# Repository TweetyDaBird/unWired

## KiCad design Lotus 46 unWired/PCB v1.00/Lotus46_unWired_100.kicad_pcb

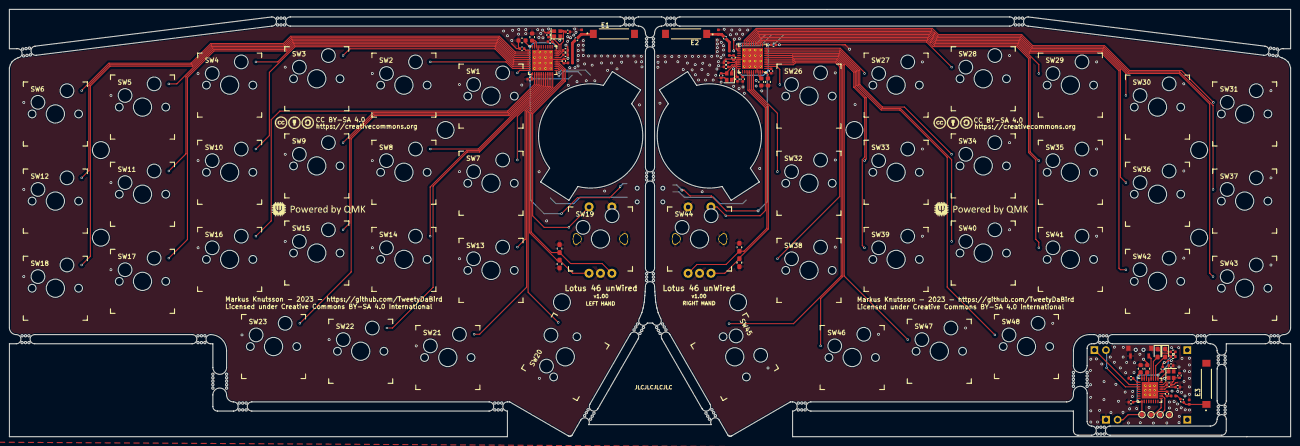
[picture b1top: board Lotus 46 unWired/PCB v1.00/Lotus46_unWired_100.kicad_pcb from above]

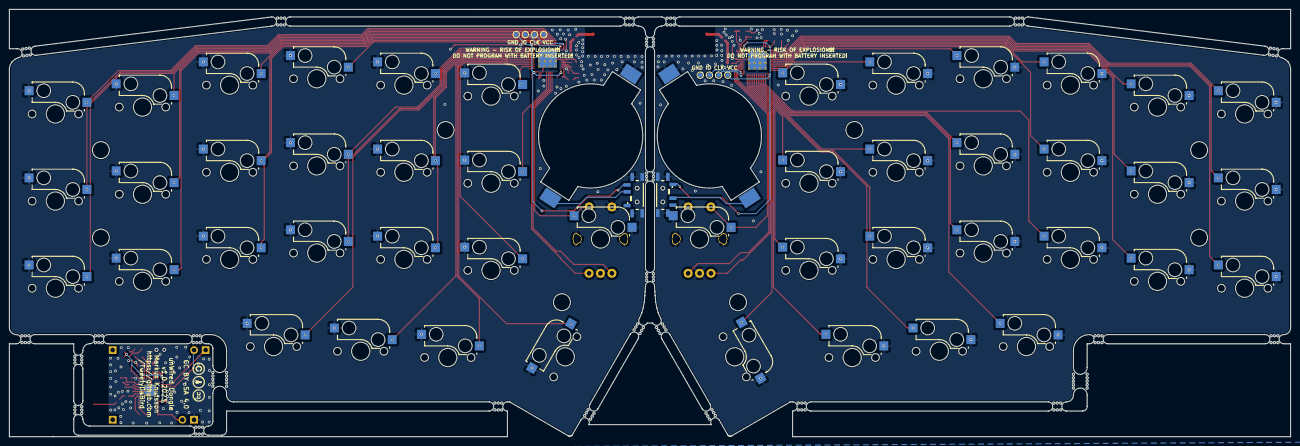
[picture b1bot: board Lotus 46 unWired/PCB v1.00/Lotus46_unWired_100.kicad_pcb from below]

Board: 2 copper layers, 280.1 x 93.4 mm, 164 parts (17 on the bottom side), 96 nets.

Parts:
BT1, BT2: Battery_Cell; BS-12
C1, C2, C7, C14, C15, C20, C30, C31, C32: 100nF; C_0402_1005Metric
C3, C16, C33: 4.7uF; C_0603_1608Metric
C4, C17, C27: 1uF; C_0603_1608Metric
C5, C18, C28: 100pF; C_0402_1005Metric
C6, C19, C29: DNP; C_0402_1005Metric
C8, C21, C34: 1.5pF; C_0402_1005Metric
C9, C22, C35: 0.8pF; C_0402_1005Metric
C10, C11, C23, C24: 100nF; C_0603_1608Metric_Pad1.08x0.95mm_HandSolder
C12, C13, C25, C26, C36, C37: 12pF; C_0402_1005Metric
E1, E2, E3: 2450AT45A100E; ANT_2450AT45A100E
J1, J2: Conn_01x02; Pinheader_2
J3, J4: Conn_01x01; PinHeader_1
L1, L2, L3, L4, L5, L6: 3.9nH; L_0402_1005Metric
LED1: RED; LED_0603_1608Metric_Pad1.05x0.95mm_HandSolder
LED2: GREEN; LED_0603_1608Metric_Pad1.05x0.95mm_HandSolder
Logo1, Logo3: QMK_Logo; qmk logo
Logo2, Logo4, Logo5: License; CC_BY_SA_40_line
PAIR1: TS-A002; YTS-A002
R1, R2: 220; R_0402_1005Metric
SW1, SW2, SW3, SW4, SW5, SW6, SW7, SW8, SW9, SW10, SW11, SW12, SW13, SW14, SW15, SW16, SW17, SW18, SW20, SW21, SW22, SW23, SW26, SW27, SW28, SW29, SW30, SW31, SW32, SW33, SW34, SW35, SW36, SW37, SW38, SW39, SW40, SW41, SW42, SW43, SW45, SW46, SW47, SW48: Switch; SW_MX_HotSwap
SW19, SW44: Switch; SW_MX_HotSwap_FOR ENCODER
SW24, SW49: Rotary_Encoder_Switch; Encoder_Alps_EC11E_Small
SW25, SW50: MSK12C02
TH1, TH2, TH3, TH4, TH5, TH6, TH7, TH8: HOLE; Spacer PCB hole
TP1, TP2, TP3, TP4, TP5, TP6, TP7, TP8, TP9, TP10, TP11, TP12: TestPoint; TestPoint_Pad_D1.0mm
U1, U2: nRF52810-QFxx; QFN-48-1EP_6x6mm_P0.4mm_EP4.6x4.6mm_ThermalVias
U3: nRF52810-QCxx; QFN-32-1EP_5x5mm_P0.5mm_EP3.6x3.6mm_ThermalVias
Y1, Y2, Y3: 7F32000E08UCG; Crystal_SMD_2016-4Pin_2.0x1.6mm
mouse-bite-2mm-slot, mouse-bite-2mm-slot#2, mouse-bite-2mm-slot#3, mouse-bite-2mm-slot#4, mouse-bite-2mm-slot#5, mouse-bite-2mm-slot#6, mouse-bite-2mm-slot#7, mouse-bite-2mm-slot#8, mouse-bite-2mm-slot#9, mouse-bite-2mm-slot#10, mouse-bite-2mm-slot#11, mouse-bite-2mm-slot#12, mouse-bite-2mm-slot#13, mouse-bite-2mm-slot#14, mouse-bite-2mm-slot#15, mouse-bite-2mm-slot#16, mouse-bite-2mm-slot#17, mouse-bite-2mm-slot#18, mouse-bite-2mm-slot#19, mouse-bite-2mm-slot#20, mouse-bite-2mm-slot#21, mouse-bite-2mm-slot#22, mouse-bite-2mm-slot#23, mouse-bite-2mm-slot#24: VAL**; mouse-bite-2mm-slot
mouse-bite-3mm-slot, mouse-bite-3mm-slot#2: VAL**; mouse-bite-3mm-slot

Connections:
+3V3: C31.2, C32.2, C33.2, J2.2, R1.2, R2.2, TP9.1, U3.9 (VDD), U3.25 (VDD), U3.32 (VDD)
/Dongle/SCL: J1.2, U3.3 (P0.01/XL2)
/Dongle/SDA: J1.1, U3.2 (P0.00/XL1)
/Dongle/SWDCLK: TP10.1, U3.17 (SWDCLK)
/Dongle/SWDIO: TP11.1, U3.18 (SWDIO)
/Left Matrix/3V3: C1.2, C2.2, C3.2, SW25.NC, TP1.1, U1.13 (VDD), U1.36 (VDD), U1.48 (VDD)
/Left Matrix/EncA: C10.1, SW24.A, U1.27 (P0.22)
/Left Matrix/EncB: C11.2, SW24.B, U1.28 (P0.23)
/Left Matrix/SW1: SW1.2, U1.12 (P0.10)
/Left Matrix/SW2: SW2.2, U1.11 (P0.09)
/Left Matrix/SW3: SW3.2, U1.10 (P0.08)
/Left Matrix/SW4: SW4.2, U1.8 (P0.06)
/Left Matrix/SW5: SW5.2, U1.5 (P0.03/AIN1)
/Left Matrix/SW6: SW6.2, U1.2 (P0.00/XL1)
/Left Matrix/SW7: SW7.2, U1.21 (P0.18)
/Left Matrix/SW8: SW8.2, U1.18 (P0.15)
/Left Matrix/SW9: SW9.2, U1.15 (P0.12)
/Left Matrix/SW10: SW10.2, U1.9 (P0.07)
/Left Matrix/SW11: SW11.2, U1.6 (P0.04/AIN2)
/Left Matrix/SW12: SW12.2, U1.3 (P0.01/XL2)
/Left Matrix/SW13: SW13.2, U1.22 (P0.19)
/Left Matrix/SW14: SW14.2, U1.19 (P0.16)
/Left Matrix/SW15: SW15.2, U1.16 (P0.13)
/Left Matrix/SW16: SW16.2, U1.14 (P0.11)
/Left Matrix/SW17: SW17.2, U1.7 (P0.05/AIN3)
/Left Matrix/SW18: SW18.2, U1.4 (P0.02/AIN0)
/Left Matrix/SW19: SW19.1, SW24.S2, U1.29 (P0.24)
/Left Matrix/SW20: SW20.2, U1.24 (P0.21/~RESET)
/Left Matrix/SW21: SW21.2, U1.23 (P0.20)
/Left Matrix/SW22: SW22.2, U1.20 (P0.17)
/Left Matrix/SW23: SW23.2, U1.17 (P0.14)
/Left Matrix/SWCLK: TP2.1, U1.25 (SWDCLK)
/Left Matrix/SWDIO: TP3.1, U1.26 (SWDIO)
/Right Matrix/3V3: C14.2, C15.2, C16.2, SW50.NO, TP5.1, U2.13 (VDD), U2.36 (VDD), U2.48 (VDD)
/Right Matrix/EncA: C23.1, SW49.A, U2.41 (P0.29/AIN5)
/Right Matrix/EncB: C24.2, SW49.B, U2.42 (P0.30/AIN6)
/Right Matrix/SW1: SW26.1, U2.2 (P0.00/XL1)
/Right Matrix/SW2: SW27.1, U2.12 (P0.10)
/Right Matrix/SW3: SW28.1, U2.14 (P0.11)
/Right Matrix/SW4: SW29.1, U2.17 (P0.14)
/Right Matrix/SW5: SW30.1, U2.20 (P0.17)
/Right Matrix/SW6: SW31.1, U2.23 (P0.20)
/Right Matrix/SW7: SW32.1, U2.43 (P0.31/AIN7)
/Right Matrix/SW8: SW33.1, U2.8 (P0.06)
/Right Matrix/SW9: SW34.1, U2.11 (P0.09)
/Right Matrix/SW10: SW35.1, U2.16 (P0.13)
/Right Matrix/SW11: SW36.1, U2.19 (P0.16)
/Right Matrix/SW12: SW37.1, U2.22 (P0.19)
/Right Matrix/SW13: SW38.1, U2.3 (P0.01/XL2)
/Right Matrix/SW14: SW39.1, U2.7 (P0.05/AIN3)
/Right Matrix/SW15: SW40.1, U2.10 (P0.08)
/Right Matrix/SW16: SW41.1, U2.15 (P0.12)
/Right Matrix/SW17: SW42.1, U2.18 (P0.15)
/Right Matrix/SW18: SW43.1, U2.21 (P0.18)
/Right Matrix/SW19: SW44.2, SW49.S1, U2.40 (P0.28/AIN4)
/Right Matrix/SW20: SW45.1, U2.4 (P0.02/AIN0)
/Right Matrix/SW21: SW46.1, U2.5 (P0.03/AIN1)
/Right Matrix/SW22: SW47.1, U2.6 (P0.04/AIN2)
/Right Matrix/SW23: SW48.1, U2.9 (P0.07)
/Right Matrix/SWCLK: TP6.1, U2.25 (SWDCLK)
/Right Matrix/SWDIO: TP7.1, U2.26 (SWDIO)
GND: BT1.2 (-), BT2.2 (-), C1.1, C2.1, C3.1, C4.1, C5.1, C6.1, C7.1, C9.1, C10.2, C11.1, C12.1, C13.2, C14.1, C15.1, C16.1, C17.1, C18.1, C19.1, C20.1, C22.1, C23.2, C24.1, C25.1, C26.2, C27.1, C28.1, C29.1, C30.1, C31.1, C32.1, C33.1, C35.1, C36.1, C37.2, J2.1, L2.1, L4.1, L6.1, PAIR1.1, PAIR1.3, SW1.1, SW2.1, SW3.1, SW4.1, SW5.1, SW6.1, SW7.1, SW8.1, SW9.1, SW10.1, SW11.1, SW12.1, SW13.1, SW14.1, SW15.1, SW16.1, SW17.1, SW18.1, SW19.2, SW19.3, SW20.1, SW21.1, SW22.1, SW23.1, SW24.C, SW24.MP1 (GND), SW24.MP2 (GND), SW24.S1, SW25.MP (GND), SW26.2, SW27.2, SW28.2, SW29.2, SW30.2, SW31.2, SW32.2, SW33.2, SW34.2, SW35.2, SW36.2, SW37.2, SW38.2, SW39.2, SW40.2, SW41.2, SW42.2, SW43.2, SW44.1, SW44.3, SW45.2, SW46.2, SW47.2, SW48.2, SW49.C, SW49.MP1 (GND), SW49.MP2 (GND), SW49.S2, SW50.MP (GND), TP4.1, TP8.1, TP12.1, U1.31 (VSS), U1.45 (VSS), U1.49 (VSS), U2.31 (VSS), U2.45 (VSS), U2.49 (VSS), U3.20 (VSS), U3.29 (VSS), U3.33 (VSS), Y1.2, Y1.4, Y2.2, Y2.4, Y3.2, Y3.4
unnamed: BT1.1 (+), SW25.COM
unnamed: BT2.1 (+), SW50.COM
unnamed: C8.1, L1.1
unnamed: C8.2, E1.1, L2.2
unnamed: C21.1, L3.1
unnamed: C21.2, E2.1, L4.2
unnamed: C34.1, L5.1
unnamed: C34.2, E3.1, L6.2
unnamed: LED1.2 (A), U3.26 (P0.25)
unnamed: LED1.1 (K), R1.1
unnamed: LED2.2 (A), U3.27 (P0.28/AIN4)
unnamed: LED2.1 (K), R2.1
unnamed: C9.2, L1.2, U1.30 (ANT)
unnamed: C4.2, U1.46 (DEC4), U1.47 (DCC)
unnamed: C7.2, U1.1 (DEC1)
unnamed: C6.2, U1.32 (DEC2)
unnamed: C5.2, U1.33 (DEC3)
unnamed: C12.2, U1.34 (XC1), Y1.3
unnamed: C13.1, U1.35 (XC2), Y1.1
unnamed: C22.2, L3.2, U2.30 (ANT)
unnamed: C17.2, U2.46 (DEC4), U2.47 (DCC)
unnamed: C20.2, U2.1 (DEC1)
unnamed: C19.2, U2.32 (DEC2)
unnamed: C18.2, U2.33 (DEC3)
unnamed: C25.2, U2.34 (XC1), Y2.3
unnamed: C26.1, U2.35 (XC2), Y2.1
unnamed: C35.2, L5.2, U3.19 (ANT)
unnamed: C27.2, U3.30 (DEC4), U3.31 (DCC)
unnamed: C30.2, U3.1 (DEC1)
unnamed: C29.2, U3.21 (DEC2)
unnamed: C28.2, U3.22 (DEC3)
unnamed: PAIR1.2, U3.28 (P0.30/AIN6)
unnamed: C36.2, U3.23 (XC1), Y3.3
unnamed: C37.1, U3.24 (XC2), Y3.1

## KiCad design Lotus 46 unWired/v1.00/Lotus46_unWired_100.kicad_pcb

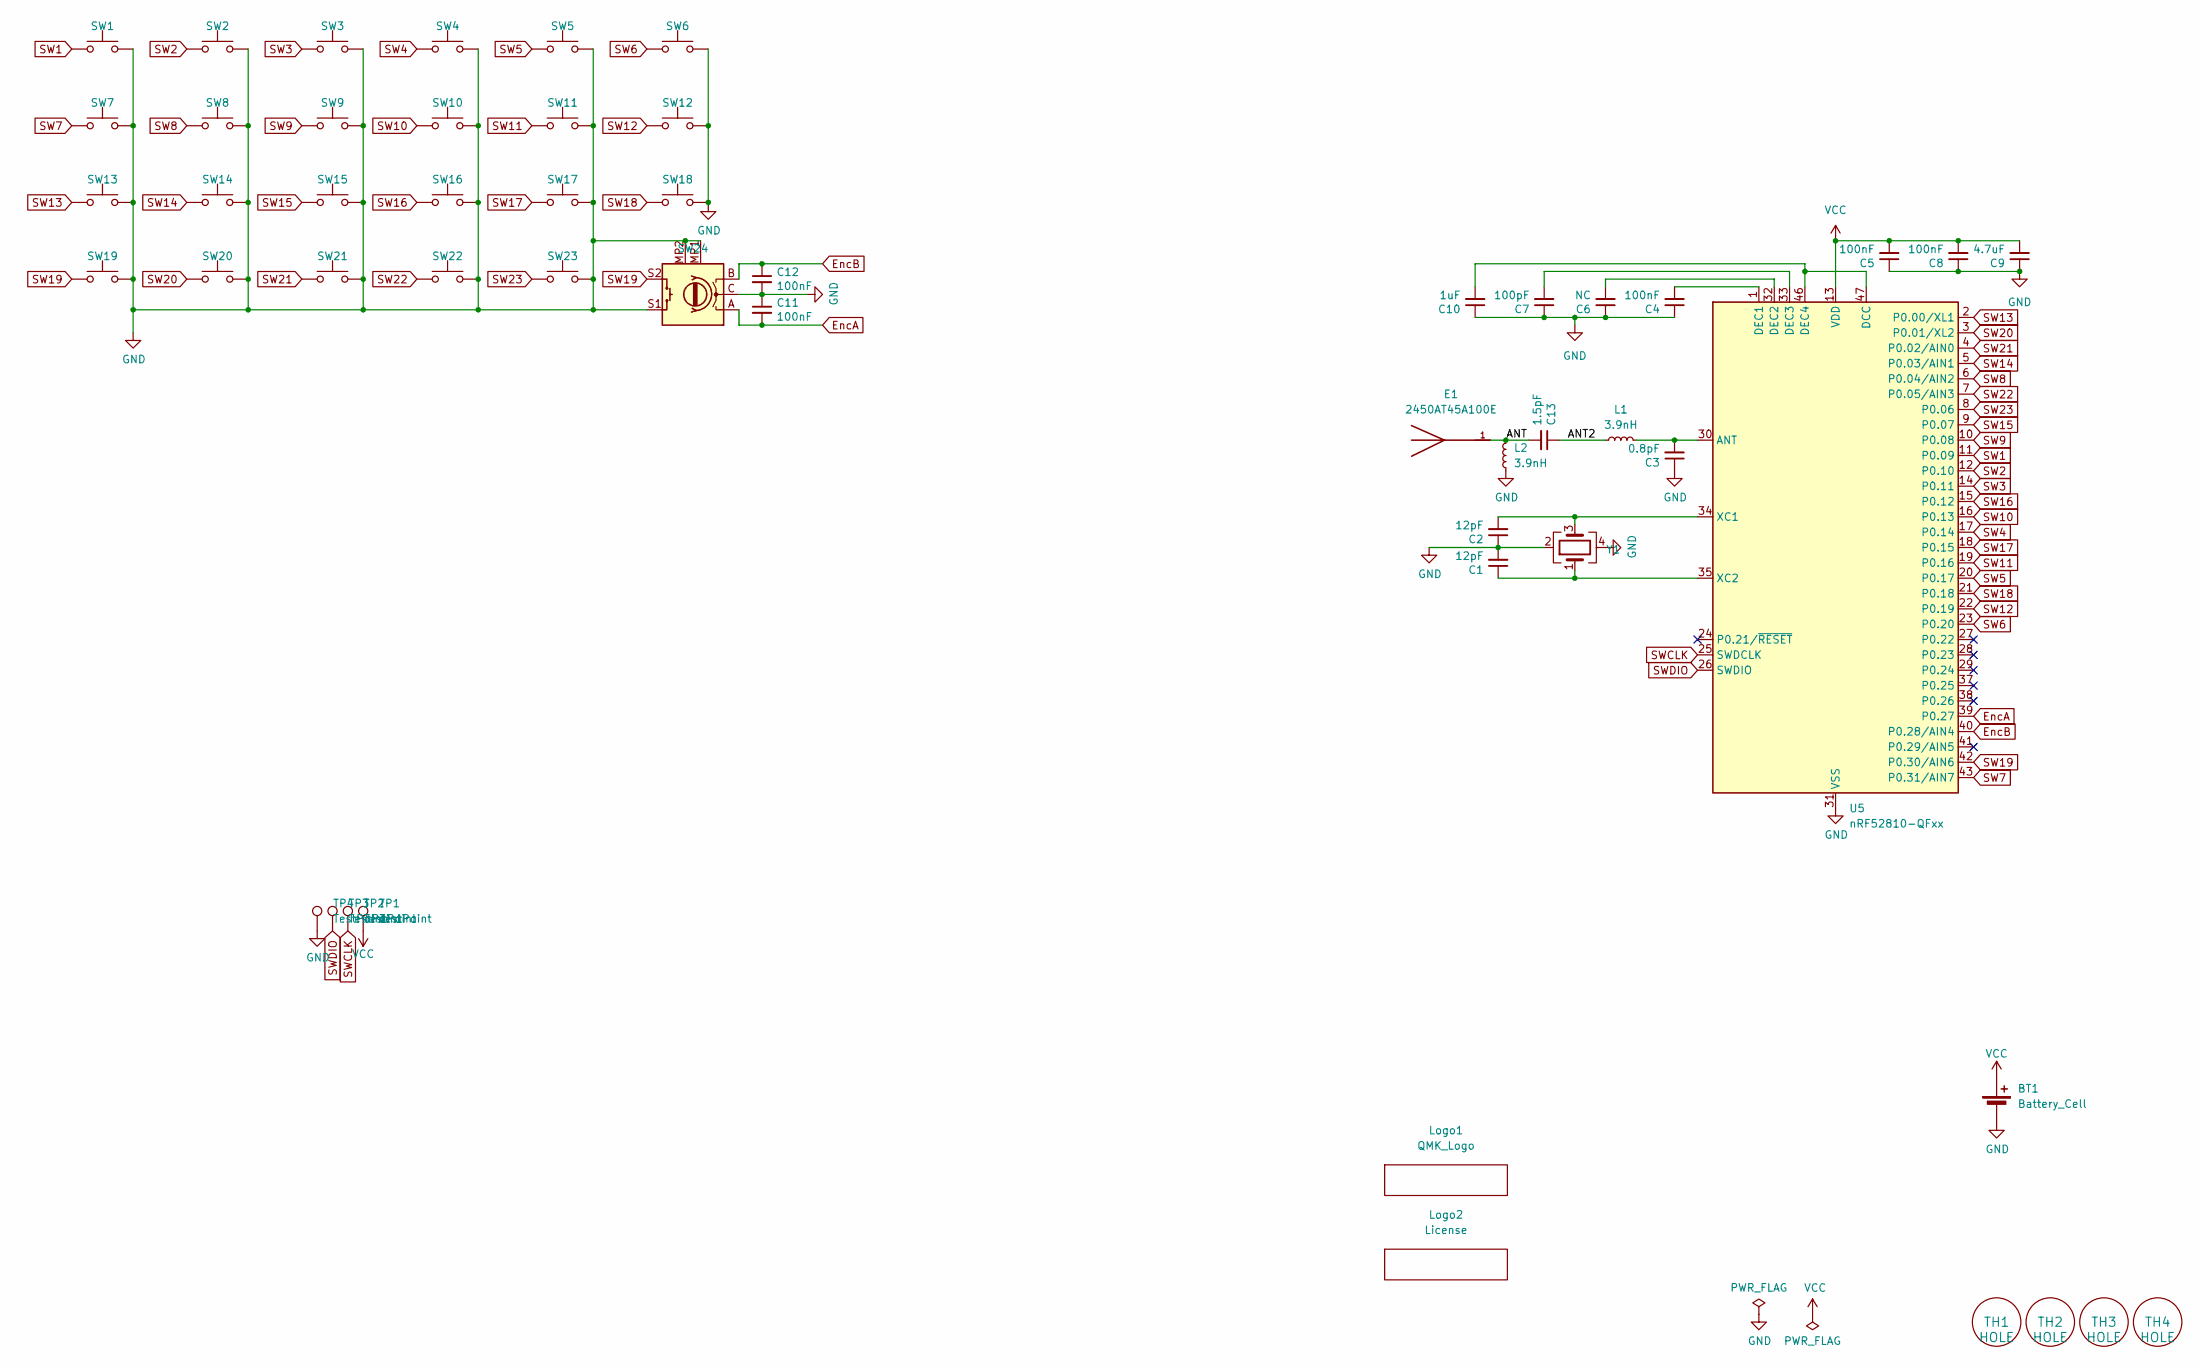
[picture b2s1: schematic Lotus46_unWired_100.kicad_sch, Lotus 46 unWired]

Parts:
BT1: Battery_Cell; BS-12
C1, C2: 12pF; C_0402_1005Metric
C3: 0.8pF; C_0402_1005Metric
C4, C5, C8: 100nF; C_0402_1005Metric
C6: NC; C_0402_1005Metric
C7: 100pF; C_0402_1005Metric
C9: 4.7uF; C_0603_1608Metric
C10: 1uF; C_0603_1608Metric
C11, C12: 100nF; C_0603_1608Metric_Pad1.08x0.95mm_HandSolder
C13: 1.5pF; C_0402_1005Metric
E1: 2450AT45A100E; ANT_2450AT45A100E; PARTREV 3.1
L1, L2: 3.9nH; L_0402_1005Metric
Logo1: QMK_Logo; qmk logo
Logo2: License; CC_BY_SA_40_line
SW1, SW2, SW3, SW4, SW5, SW6, SW7, SW8, SW9, SW10, SW11, SW12, SW13, SW14, SW15, SW16, SW17, SW18, SW19, SW20, SW21, SW22, SW23: Switch; SW_MX_HotSwap_Reversible
SW24: Rotary_Encoder_Switch; Encoder_Alps_EC11E_Small
TH1, TH2, TH3, TH4: HOLE; Spacer PCB hole
TP1, TP2, TP3, TP4: TestPoint; TestPoint_Pad_D1.0mm
U5: nRF52810-QFxx; QFN-48-1EP_6x6mm_P0.4mm_EP4.6x4.6mm_ThermalVias
Y1: Crystal_SMD_2016-4Pin_2.0x1.6mm

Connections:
/ANT: C13.2, E1.1, L2.2
/ANT2: C13.1, L1.1
EncA: C11.2, SW24.A, U5.39 (P0.27)
EncB: C12.1, SW24.B, U5.40 (P0.28/AIN4)
GND: BT1.2 (-), C1.2, C2.1, C3.1, C4.1, C5.1, C6.1, C7.1, C8.1, C9.1, C10.1, C11.1, C12.2, L2.1, SW1.2, SW2.2, SW3.2, SW4.2, SW5.2, SW6.2, SW7.2, SW8.2, SW9.2, SW10.2, SW11.2, SW12.2, SW13.2, SW14.2, SW15.2, SW16.2, SW17.2, SW18.2, SW19.2, SW20.2, SW21.2, SW22.2, SW23.2, SW24.C, SW24.MP1 (GND), SW24.MP2 (GND), SW24.S1, TP4.1, U5.31 (VSS), U5.45 (VSS), U5.49 (VSS), Y1.2, Y1.4
unnamed: C3.2, L1.2, U5.30 (ANT)
unnamed: C10.2, U5.46 (DEC4), U5.47 (DCC)
unnamed: C4.2, U5.1 (DEC1)
unnamed: C6.2, U5.32 (DEC2)
unnamed: C7.2, U5.33 (DEC3)
unnamed: C2.2, U5.34 (XC1), Y1.3
unnamed: C1.1, U5.35 (XC2), Y1.1
SW1: SW1.1, U5.11 (P0.09)
SW2: SW2.1, U5.12 (P0.10)
SW3: SW3.1, U5.14 (P0.11)
SW4: SW4.1, U5.17 (P0.14)
SW5: SW5.1, U5.20 (P0.17)
SW6: SW6.1, U5.23 (P0.20)
SW7: SW7.1, U5.43 (P0.31/AIN7)
SW8: SW8.1, U5.6 (P0.04/AIN2)
SW9: SW9.1, U5.10 (P0.08)
SW10: SW10.1, U5.16 (P0.13)
SW11: SW11.1, U5.19 (P0.16)
SW12: SW12.1, U5.22 (P0.19)
SW13: SW13.1, U5.2 (P0.00/XL1)
SW14: SW14.1, U5.5 (P0.03/AIN1)
SW15: SW15.1, U5.9 (P0.07)
SW16: SW16.1, U5.15 (P0.12)
SW17: SW17.1, U5.18 (P0.15)
SW18: SW18.1, U5.21 (P0.18)
SW19: SW19.1, SW24.S2, U5.42 (P0.30/AIN6)
SW20: SW20.1, U5.3 (P0.01/XL2)
SW21: SW21.1, U5.4 (P0.02/AIN0)
SW22: SW22.1, U5.7 (P0.05/AIN3)
SW23: SW23.1, U5.8 (P0.06)
SWCLK: TP2.1, U5.25 (SWDCLK)
SWDIO: TP3.1, U5.26 (SWDIO)
VCC: BT1.1 (+), C5.2, C8.2, C9.2, TP1.1, U5.13 (VDD), U5.36 (VDD), U5.48 (VDD)

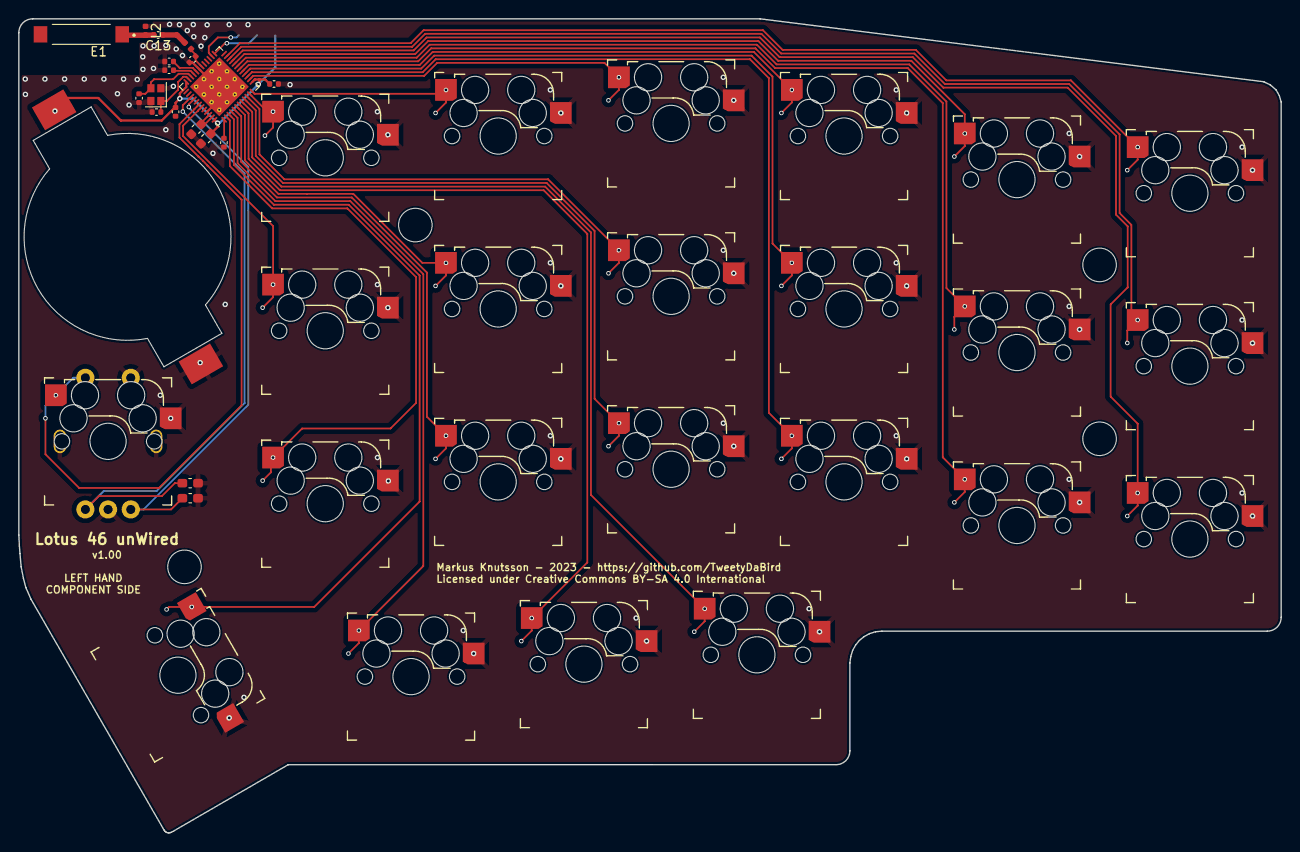
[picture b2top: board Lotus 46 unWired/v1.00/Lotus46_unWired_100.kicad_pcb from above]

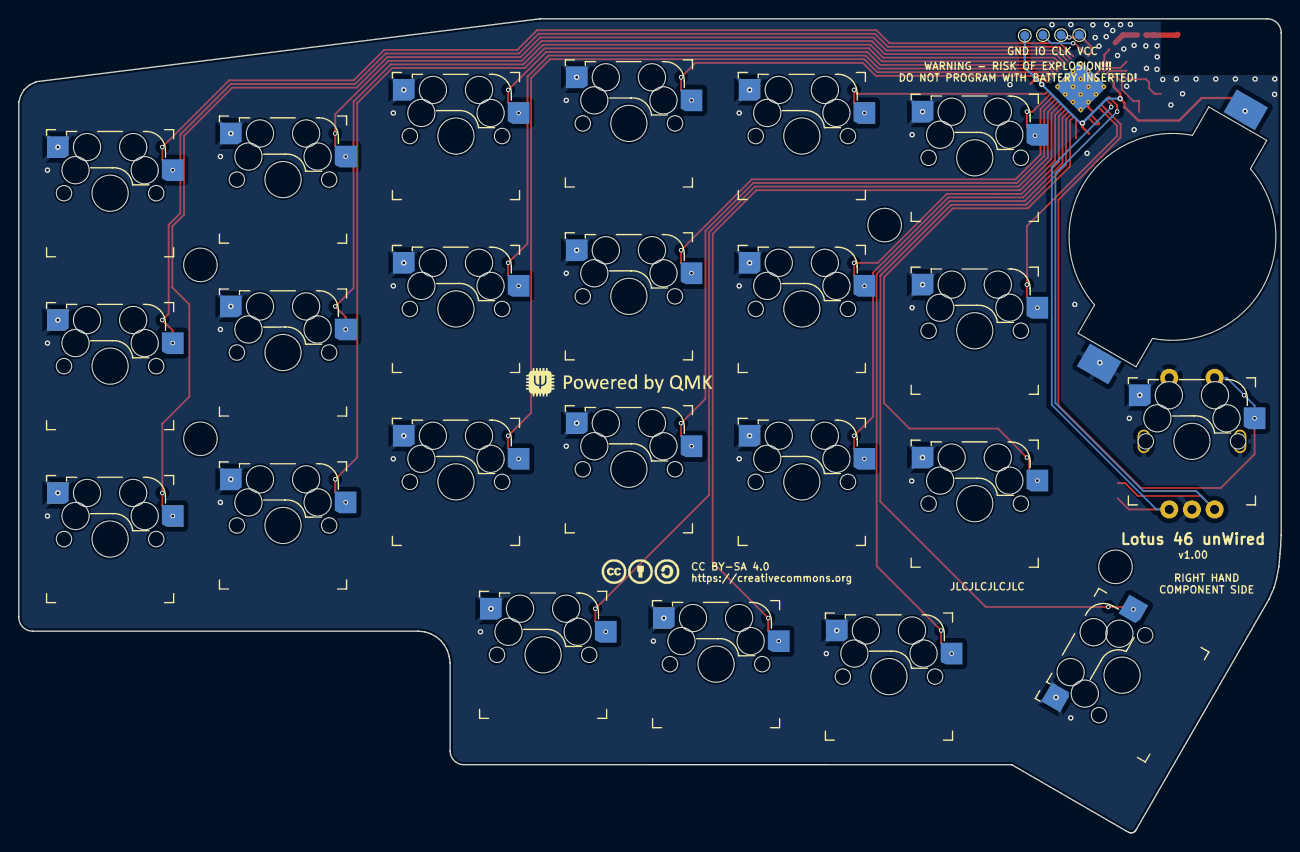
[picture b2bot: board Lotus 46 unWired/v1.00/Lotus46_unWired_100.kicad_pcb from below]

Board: 2 copper layers, 139.1 x 89.7 mm, 53 parts (6 on the bottom side), 38 nets.

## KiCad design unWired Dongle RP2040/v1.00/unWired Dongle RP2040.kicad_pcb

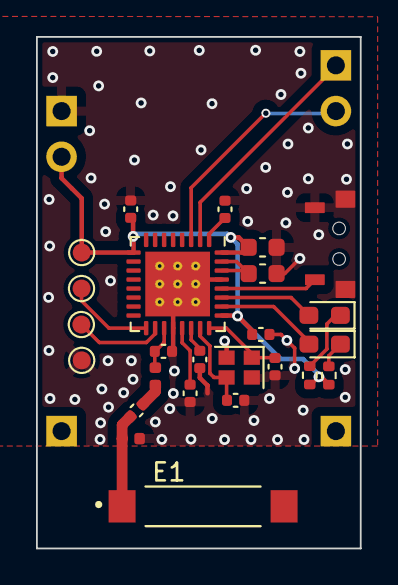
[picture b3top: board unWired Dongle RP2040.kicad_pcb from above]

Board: 2 copper layers, 18.0 x 28.4 mm, 30 parts (1 on the bottom side), 20 nets.

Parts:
C1, C2: 12pF; C_0402_1005Metric
C3: 0.8pF; C_0402_1005Metric
C4, C5, C8: 100nF; C_0402_1005Metric
C6: NC; C_0402_1005Metric
C7: 100pF; C_0402_1005Metric
C9: 4.7uF; C_0603_1608Metric
C10: 1uF; C_0603_1608Metric
C11: 1.5pF; C_0402_1005Metric
E1: 2450AT45A100E; ANT_2450AT45A100E
J1, J2: Conn_01x02; PinHeader_1x02_P2.54mm_Vertical
J3, J4: Conn_01x01; PinHeader_1x01_P2.54mm_Vertical
L1, L2: 3.9nH; L_0402_1005Metric
LED1: RED; LED_0603_1608Metric_Pad1.05x0.95mm_HandSolder
LED2: GREEN; LED_0603_1608Metric_Pad1.05x0.95mm_HandSolder
Logo2: License; CC_BY_SA_40_line
PAIR1: TS-A002; YTS-A002
R1, R2: 220; R_0402_1005Metric
TP1, TP2, TP3, TP4: TestPoint; TestPoint_Pad_D1.0mm
U1: nRF52810-QCxx; QFN-32-1EP_5x5mm_P0.5mm_EP3.6x3.6mm_ThermalVias
Y1: Crystal_SMD_2016-4Pin_2.0x1.6mm

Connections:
/SCL: J1.2, U1.3 (P0.01/XL2)
/SDA: J1.1, U1.2 (P0.00/XL1)
/SWDCLK: TP3.1, U1.17 (SWDCLK)
/SWDIO: TP2.1, U1.18 (SWDIO)
GND: C1.2, C2.1, C3.1, C4.1, C5.1, C6.1, C7.1, C8.1, C9.1, C10.1, J2.1, L2.1, PAIR1.1, PAIR1.3, TP1.1, U1.20 (VSS), U1.29 (VSS), U1.33 (VSS), Y1.2, Y1.4
unnamed: C11.1, L1.1
unnamed: C11.2, E1.1, L2.2
unnamed: LED1.2 (A), U1.26 (P0.25)
unnamed: LED1.1 (K), R1.1
unnamed: LED2.2 (A), U1.27 (P0.28/AIN4)
unnamed: LED2.1 (K), R2.1
unnamed: C3.2, L1.2, U1.19 (ANT)
unnamed: C10.2, U1.30 (DEC4), U1.31 (DCC)
unnamed: C4.2, U1.1 (DEC1)
unnamed: C6.2, U1.21 (DEC2)
unnamed: C7.2, U1.22 (DEC3)
unnamed: PAIR1.2, U1.28 (P0.30/AIN6)
unnamed: C2.2, U1.23 (XC1), Y1.3
unnamed: C1.1, U1.24 (XC2), Y1.1
VCC: C5.2, C8.2, C9.2, J2.2, R1.2, R2.2, TP4.1, U1.9 (VDD), U1.25 (VDD), U1.32 (VDD)

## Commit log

2023-08-21 Initial commit Dongle
2023-08-21 edit ignore
2023-08-21 Initial Commit Lotus58 uW
2023-08-21 Initial Commit Lotus46 uW
2023-08-21 Moved files
2023-08-21 Silcscreen correction
2023-08-25 Add license
2023-09-12 gitignore
2023-09-12 git ignore
2023-09-12 Test
2023-09-12 Cleanup plate
2023-09-12 Cleanup old readme

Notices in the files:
Lotus 46 unWired/PCB v1.00/Lotus46_unWired_100.kicad_pcb:
Licensed under Creative Commons BY-SA 4.0 International
